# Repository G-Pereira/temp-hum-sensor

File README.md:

# Temperature and Humidity wireless and battery operated sensor

Features an ESP-12F (ESP8266) and a Texas Instruments HDC1080 or HDC2080 and runs out of a CR2477 coin battery cell.

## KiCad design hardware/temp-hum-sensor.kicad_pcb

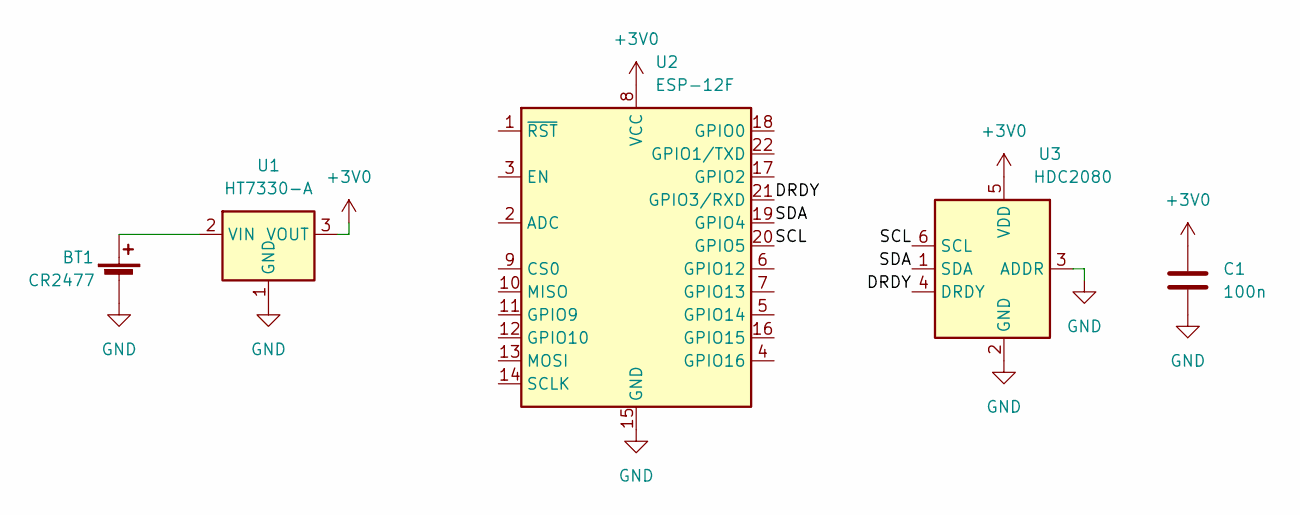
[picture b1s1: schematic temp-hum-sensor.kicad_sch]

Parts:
BT1: CR2477
C1: 100n; R_0805_2012Metric; LCSC C49678
U1: HT7330-A; SOT-89-3; LCSC C347190
U2: ESP-12F; ESP-12E; LCSC C82891
U3: HDC2080; Texas_PWSON-N6; LCSC C82227

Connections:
+3V0: C1.1, U1.3 (VOUT), U2.8 (VCC), U3.5 (VDD)
/DRDY: U2.21 (GPIO3/RXD), U3.4 (DRDY)
/SCL: U2.20 (GPIO5), U3.6 (SCL)
/SDA: U2.19 (GPIO4), U3.1 (SDA)
GND: BT1.2 (-), C1.2, U1.1 (GND), U2.15 (GND), U3.2 (GND), U3.3 (ADDR)
unnamed: BT1.1 (+), U1.2 (VIN)

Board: 2 copper layers, 5 parts (1 on the bottom side), 6 nets, no tracks yet.

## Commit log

2021-12-15 Add README
2021-12-15 Updated PCB
